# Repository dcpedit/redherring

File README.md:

# Red Herring Keyboard

Red Herring is a 75% ortholinear keyboard with staggered columns and a split ergonomic layout similar to an Arisu/Alice.  Here you will find the KiCad 6 files for the PCB and plate, along with Illustrator files for the case and wrist rest. Keyboard features:
- Through-hole or hotswap socket variants
- Diodes arranged in a unique herringbone pattern
- Large rotary encoder knob (up to 48mm diameter)
- 64x128 OLED display (SSD1107)
- Compatible with most standard keycap sets (1.75u for left shift, and 2u for left space)
- Different [layout options](http://www.keyboard-layout-editor.com/#/gists/cf2afd92ae2ac742f6cb94146715b537), including ISO

## Firmware ([Vial](https://get.vial.today/)):

If you're flashing a brand new MCU, you will need to use an ISP programmer to install a bootloader first. I didn't have an AVR ISP programmer, so I flashed a spare Elite-C to do this.

Look in the `firmware` folder for hex files and more info on flashing.

## Photos:

## Thanks!
This project would not have been possible without the time and dedication of everyone who worked on the amazing keyboards I learned and took inspiration from.  To name a few: Jabberwocky, Boardrun, Basketweave, Adelheid, Mercutio, Discipline, and Mysterium.

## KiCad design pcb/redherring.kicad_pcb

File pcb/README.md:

# Red Herring PCB
The files here were created with KiCad 6.

## Manufacturing
I used JLCPCB.com to get this manufactured.  They have [a good tutorial](https://support.jlcpcb.com/article/149-how-to-generate-gerber-and-drill-files-in-kicad) on how to generate the Gerber files from KiCad. If the website is not able to calculate the dimensions, you can enter it in manually.  Here are the details

- Size: 364.4 mm x 167.2 mm
- Thickness: 1.6 mm FR4
- 2 Layers

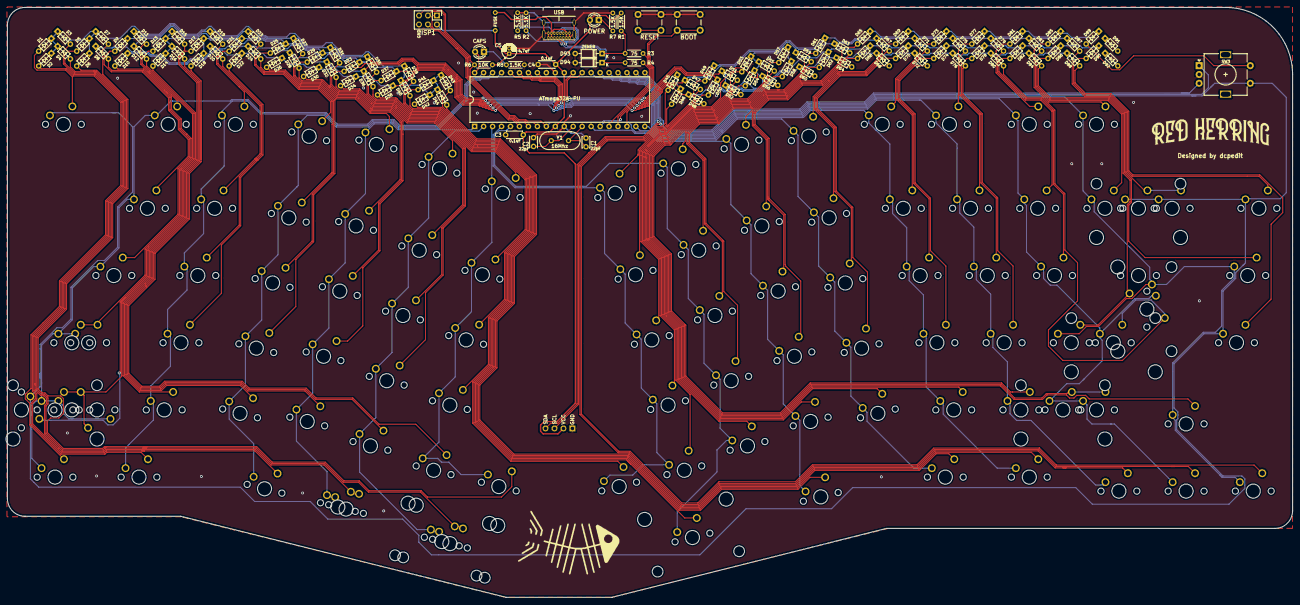
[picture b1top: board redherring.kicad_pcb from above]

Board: 2 copper layers, 364.4 x 167.2 mm, 216 parts (0 on the bottom side), 134 nets.

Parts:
BOOT: SW_Push; SW_PUSH_6mm
C1, C2: 22pF; C_Disc_D3.0mm_W2.0mm_P2.50mm
C3, C4: 0.1uF; C_Disc_D4.3mm_W1.9mm_P5.00mm
C5: 4.7uF; CP_Radial_D4.0mm_P1.50mm
CAPS: LED; LED_D3.0mm_Clear
D1, D2, D3, D4, D5, D6, D7, D8, D9, D10, D11, D12, D13, D14, D15, D16, D17, D18, D19, D20, D21, D22, D23, D24, D25, D26, D27, D28, D29, D30, D31, D32, D33, D34, D35, D36, D37, D38, D39, D40, D41, D42, D43, D44, D45, D46, D47, D48, D49, D50, D51, D52, D53, D54, D55, D56, D57, D58, D59, D60, D61, D62, D63, D64, D65, D66, D67, D68, D69, D70, D71, D72, D73, D74, D75, D76, D77, D78, D79, D80, D81, D82, D83, D84, D85, D86, D87, D88, D89, D90, D91, D92: D_Small; D_DO-35_SOD27_P5.08mm_Horizontal
D93, D94: 3.6V; D_DO-35_SOD27_P7.62mm_Horizontal
F1: 500mA; polyfuse_5.1mm
ISP1: AVR-ISP-6; PinHeader_2x03_P2.54mm_Vertical
J2: OLED; SSD1306_OLED
MX101, MX102, MX103, MX104, MX105, MX106, MX107, MX108, MX109, MX110, MX111, MX112, MX113, MX114, MX201, MX202, MX203, MX204, MX205, MX206, MX207, MX208, MX209, MX210, MX211, MX212, MX213, MX214, MX215, MX302, MX303, MX304, MX305, MX306, MX307, MX308, MX309, MX310, MX311, MX312, MX313, MX314, MX315, MX402, MX403, MX404, MX405, MX406, MX407, MX408, MX409, MX410, MX411, MX412, MX414, MX415, MX501, MX502, MX503, MX504, MX505, MX506, MX507, MX508, MX509, MX510, MX511, MX512, MX514, MX515, MX604.1, MX606, MX607, MX612, MX613, MX614, MX615: MX-NoLED; MXOnly-1U-NoLED
MX215.2: MX-NoLED; MXOnly-2U-NoLED
MX301, MX314.150: MX-NoLED; MXOnly-1.5U-NoLED
MX401, MX501.175: MX-NoLED; MXOnly-1.75U-NoLED
MX401.125, MX513, MX601, MX602, MX603, MX604, MX609, MX610, MX611: MX-NoLED; MXOnly-1.25U-NoLED
MX413: MX-NoLED; MXOnly-ISO-ROTATED-ReversedStabilizers-NoLED
MX413.225, MX501.225, MX513.225: MX-NoLED; MXOnly-2.25U-NoLED
MX605: MX-NoLED; MXOnly-2U-ReversedStabilizers-NoLED
MX605.225: MX-NoLED; MXOnly-2.25U-ReversedStabilizers-NoLED
MX608: MX-NoLED; MXOnly-2.75U-ReversedStabilizers-NoLED
POWER: LED; LED_D3.0mm_Clear
R1, R7, R8: 1.5K; R_Axial_DIN0204_L3.6mm_D1.6mm_P5.08mm_Horizontal
R2, R5: 5.1K; R_Axial_DIN0204_L3.6mm_D1.6mm_P5.08mm_Horizontal
R3, R4: 75; R_Axial_DIN0204_L3.6mm_D1.6mm_P5.08mm_Horizontal
R6: 10K; R_Axial_DIN0204_L3.6mm_D1.6mm_P5.08mm_Horizontal
RESET: SW_Push; SW_PUSH_6mm
SW3: Rotary_Encoder_Switch; RotaryEncoder_Alps_EC11E-Switch_Vertical_H20mm
U1: ATmega32A-PU; DIP-40_W15.24mm
USB: USB_C_GCT_USB4085-Type-C; USB_C_GCT_USB4085
Y1: 16Mhz; Crystal_HC49-4H_Vertical

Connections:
+5V: C3.1, C4.1, C5.1, F1.1, ISP1.2, J2.2, POWER.2, R1.1, R6.1, U1.10, U1.30
CAPSLOCK: CAPS.2, U1.40
COL0: MX101.1, MX201.1, MX301.1, MX401.1, MX401.125.1, MX501.1, MX501.175.1, MX501.225.1, MX601.1, U1.39
COL1: MX102.1, MX202.1, MX302.1, MX402.1, MX502.1, MX602.1, U1.38
COL2: MX103.1, MX203.1, MX303.1, MX403.1, MX503.1, MX603.1, U1.37
COL3: MX104.1, MX204.1, MX304.1, MX404.1, MX504.1, MX604.1, MX604.1.1, U1.1
COL4: MX105.1, MX205.1, MX305.1, MX405.1, MX505.1, MX605.1, MX605.225.1, U1.2
COL5: MX106.1, MX206.1, MX306.1, MX406.1, MX506.1, MX606.1, U1.3
COL6: MX107.1, MX207.1, MX307.1, MX407.1, MX507.1, MX607.1, U1.4
COL7: MX108.1, MX208.1, MX308.1, MX408.1, MX508.1, MX608.1, U1.5
COL8: MX109.1, MX209.1, MX309.1, MX409.1, MX509.1, MX609.1, U1.14
COL9: MX110.1, MX210.1, MX310.1, MX410.1, MX510.1, MX610.1, U1.15
COL10: MX111.1, MX211.1, MX311.1, MX411.1, MX511.1, MX611.1, U1.19
COL11: MX112.1, MX212.1, MX312.1, MX412.1, MX512.1, MX612.1, U1.20
COL12: MX113.1, MX213.1, MX313.1, MX413.1, MX413.225.1, MX513.1, MX513.225.1, MX613.1, U1.27
COL13: MX114.1, MX214.1, MX314.1, MX314.150.1, MX414.1, MX514.1, MX614.1, U1.26
COL14: MX215.1, MX215.2.1, MX315.1, MX415.1, MX515.1, MX615.1, SW3.S1, U1.25
D+: R4.1, U1.16
D-: R3.1, U1.17
EN1: SW3.A, U1.24
EN2: SW3.B, U1.21
GND: BOOT.1, C1.1, C2.1, C3.2, C4.2, C5.2, D93.2, D94.2, ISP1.6, J2.1, R2.1, R5.1, R7.2, R8.2, RESET.1, SW3.C, U1.11, U1.31, USB.A1, USB.A12, USB.B1, USB.B12, USB.S1
MISO: ISP1.1, U1.7
MOSI: ISP1.4, U1.6
unnamed: C1.2, U1.13, Y1.1
unnamed: C2.2, U1.12, Y1.2
unnamed: CAPS.1, R8.1
unnamed: D1.2, MX615.2
unnamed: D2.2, MX601.2
unnamed: D3.2, MX602.2
unnamed: D4.2, MX604.2, MX604.1.2
unnamed: D5.2, MX603.2
unnamed: D6.2, MX605.2, MX605.225.2
unnamed: D7.2, MX606.2
unnamed: D8.2, MX301.2
unnamed: D9.2, MX201.2
unnamed: D10.2, MX401.2, MX401.125.2
unnamed: D11.2, MX101.2
unnamed: D12.2, MX501.2, MX501.175.2, MX501.225.2
unnamed: D13.2, MX515.2
unnamed: D14.2, MX502.2
unnamed: D15.2, MX503.2
unnamed: D16.2, MX505.2
unnamed: D17.2, MX504.2
unnamed: D18.2, MX506.2
unnamed: D19.2, MX102.2
unnamed: D20.2, MX302.2
unnamed: D21.2, MX202.2
unnamed: D22.2, MX402.2
unnamed: D23.2, MX103.2
unnamed: D24.2, MX303.2
unnamed: D25.2, MX203.2
unnamed: D26.2, MX403.2
unnamed: D27.2, MX104.2
unnamed: D28.2, MX304.2
unnamed: D29.2, MX204.2
unnamed: D30.2, MX404.2
unnamed: D31.2, MX105.2
unnamed: D32.2, MX305.2
unnamed: D33.2, MX205.2
unnamed: D34.2, MX405.2
unnamed: D35.2, MX106.2
unnamed: D36.2, MX306.2
unnamed: D37.2, MX206.2
unnamed: D38.2, MX406.2
unnamed: D39.2, MX607.2
unnamed: D40.2, MX609.2
unnamed: D41.2, MX608.2
unnamed: D42.2, MX610.2
unnamed: D43.2, MX611.2
unnamed: D44.2, MX612.2
unnamed: D45.2, MX613.2
unnamed: D46.2, MX614.2
unnamed: D47.2, MX207.2
unnamed: D48.2, MX407.2
unnamed: D49.2, MX107.2
unnamed: D50.2, MX307.2
unnamed: D51.2, MX508.2
unnamed: D52.2, MX510.2
unnamed: D53.2, MX507.2
unnamed: D54.2, MX509.2
unnamed: D55.2, MX514.2
unnamed: D56.2, MX512.2
unnamed: D57.2, MX511.2
unnamed: D58.2, MX513.2, MX513.225.2
unnamed: D59.2, MX208.2
unnamed: D60.2, MX408.2
unnamed: D61.2, MX108.2
unnamed: D62.2, MX308.2
unnamed: D63.2, MX209.2
unnamed: D64.2, MX409.2
unnamed: D65.2, MX109.2
unnamed: D66.2, MX309.2
unnamed: D67.2, MX210.2
unnamed: D68.2, MX410.2
unnamed: D69.2, MX110.2
unnamed: D70.2, MX310.2
unnamed: D71.2, MX211.2
unnamed: D72.2, MX411.2
unnamed: D73.2, MX111.2
unnamed: D74.2, MX311.2
unnamed: D75.2, MX212.2
unnamed: D76.2, MX412.2
unnamed: D77.2, MX112.2
unnamed: D78.2, MX312.2
unnamed: D79.2, MX213.2
unnamed: D80.2, MX413.2, MX413.225.2
unnamed: D81.2, MX113.2
unnamed: D82.2, MX313.2
unnamed: D83.2, MX214.2
unnamed: D84.2, MX414.2
unnamed: D85.2, MX114.2
unnamed: D86.2, MX314.2, MX314.150.2
unnamed: D87.2, MX215.2, MX215.2.2
unnamed: D88.2, MX415.2
unnamed: D89.2, SW3.S2
unnamed: D90.2, MX315.2
unnamed: D93.1, R1.2, R3.2, USB.A7, USB.B7
unnamed: D94.1, R4.2, USB.A6, USB.B6
unnamed: POWER.1, R7.1
unnamed: R2.2, USB.A5
unnamed: R5.2, USB.B5
ROW0: D11.1, D19.1, D23.1, D27.1, D31.1, D35.1, D49.1, D61.1, D65.1, D69.1, D73.1, D77.1, D81.1, D85.1, D89.1, U1.28
ROW1: D9.1, D21.1, D25.1, D29.1, D33.1, D37.1, D47.1, D59.1, D63.1, D67.1, D71.1, D75.1, D79.1, D83.1, D87.1, U1.34
ROW2: D8.1, D20.1, D24.1, D28.1, D32.1, D36.1, D50.1, D62.1, D66.1, D70.1, D74.1, D78.1, D82.1, D86.1, D90.1, U1.33
ROW3: D10.1, D22.1, D26.1, D30.1, D34.1, D38.1, D48.1, D60.1, D64.1, D68.1, D72.1, D76.1, D80.1, D84.1, D88.1, U1.36
ROW4: D12.1, D13.1, D14.1, D15.1, D16.1, D17.1, D18.1, D51.1, D52.1, D53.1, D54.1, D55.1, D56.1, D57.1, D58.1, U1.29
ROW5: D1.1, D2.1, D3.1, D4.1, D5.1, D6.1, D7.1, D39.1, D40.1, D41.1, D42.1, D43.1, D44.1, D45.1, D46.1, U1.35
SCK: ISP1.3, U1.8
SCL: J2.3, U1.22
SDA: J2.4, U1.23
VCC: F1.2, USB.A4, USB.A9, USB.B4, USB.B9
boot: BOOT.2, U1.18
reset: ISP1.5, R6.2, RESET.2, U1.9

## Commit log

2022-03-16 Remove design file
2022-03-16 Add thanks section
2022-03-17 Add readme for case
2022-03-18 Add solenoid edition top
2022-03-20 Update with parts links
2022-03-21 Add pcb details, case stickers
2022-03-21 Add info to case
2022-03-21 Acrylic description for wrist rest
2022-03-21 Add clear top for solenoid edition
2022-03-21 Description for foam layers
2022-03-21 Mention shortening OLED header
2022-03-24 Add firmware hex and readme
2022-03-25 Generate gerber files
2022-04-06 Firmware readme update
2022-04-07 Update firmware readme
2022-04-09 Update readmes
2022-04-16 firmware with solenoid support
2022-04-18 Clarify ISP pins
2022-05-12 Add instructions for updating OLED graphic
2022-05-15 fix screw info
2022-08-08 Update component links
2022-09-10 Updated OLED link on BOM
    Old oled link was dead, replaced with a new link. (Product selected is arbitrary it was a top search result). Tracking code was removed from the URL. Added OLED Resolution to the BOM title.
2022-09-10 Added EC11 Alternate link
    Digikey has the preferred EC11 rotary encoder on back order. Mouser has them in stock, so I added a mouser link.
2022-09-11 Added alternative link for ATmega32A
    Added mouser link for ATmega32A.
2022-09-11 Added alternate link for usb-c port
2022-09-11 Added 10k Resistor alternate link
    Preferred 10k resistor has a long lead time. Alternative link added.
2022-10-30 Add hotswap pcb variant
    Changed through-hole mx switch footprints to hotswap. Re-routed PCB and validated against Design Rules Checker.
2022-11-04 Update readme.
2022-11-18 Update README.md
    Fix typo
2022-12-01 Update readme now that manufactured hotswap pcb has been tested.
2022-12-04 Add more specificity to the oled in the bill of materials.
2023-01-18 Atmega flash guide
2023-01-18 Add flash guide link
2023-04-18 Initial commit red herring V2
2023-04-18 All diodes placed
2023-04-19 Fixed columns started LED wiring and routing
2023-04-19 LED wiring first pass complete
2023-04-19 First pass wiring complete reworked pimoroni fixed outline
2023-04-20 Updated diode footprint updated 3d models for diode and tip120
2023-04-20 Added 3d models
2023-04-20 Pimoroni removed key outlines added for odd sized keys
2023-04-21 Placed two additional keys
2023-04-21 Outline reduced to 1.5mm
2023-04-21 Added readme Added images Added gerbers PCB DRC cleanup Added teardrops and rebuilt zones
2023-08-14 Update Left shift cluster to not overlap with BSLSH
2023-08-15 Add 3d models and update ISO enter to also be hotswap
2023-08-17 Update with corrected placement and ISO Enter hotswap. Update plate - WIP
2023-10-12 Fix plate foam
2023-11-03 Update README.md github link
2023-11-06 Add QMK & Via firmware
2023-11-14 Add VIA file and links
2024-05-08 Update firmware graphic instructions
